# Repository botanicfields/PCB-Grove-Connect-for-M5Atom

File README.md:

# PCB-Grove-for-M5Atom
a PCB to add 3 Grove Connectors to M5Atom

# M5Atom 用 GROVE コネクタ基板

M5Atom のピンソケット (GPIO) を GROVE コネクタに変換する基板です。
GROVE ケーブルによるデバイスの接続が簡単になります。

委託販売（スイッチサイエンス）：  
https://www.switch-science.com/catalog/7309/

## 1. 特徴

- 基板上のピンヘッダに M5Atom Lite/Matrix を直接接続できます。
- M5Atom の GPIO を GROVE コネクタ 3 個で取り出せます。M5Atom の Grove ポートと合わせて計 4 ポートとなります。
- M5Atom のピンソケットを、基板上のピンソケットから取り出せます。
- DC ジャック (5V) があり、USB-C ケーブルと同時または単独でも給電できます。DCジャックからの電源にはフューズがあります。
- ディップスイッチで、一部プルアップ抵抗/保護抵抗の接続/バイパスができます。

※ 動作中の電源の抜き差し (USB-C / DC ジャック) は、動作継続を保証できません。

## 2. ご注意

- M5Atom は付属しません。
- AC アダプタは付属しません。
- GROVE ケーブルは付属しません。
- ディップスイッチの切り替えには、ピンセット等が必要です。
- プリント基板単体の完成品です。ケースや足は付属しません。裏面からピンが飛び出しています。絶縁材や四隅の穴にスペーサを取り付けるなどして、負傷、静電気破壊、机などの傷を防止してください。

## 使用例
「ENV ユニット」(I2C)、「M5 用光センサ・押しボタン 5 基板」(アナログ)、「DFPlayer-Mini用 Grove 接続基板」(UART) を同時接続し、USB-C または DC 5V 電源を接続しています。動作に使用したプログラム BF-030.ino は、温度・湿度・気圧・周囲の明るさをシリアルモニタに定期的に表示する一方、押しボタンで楽曲の演奏を制御（次の曲、前の曲、音量増、音量減、USB/microSD 切替）できます。

## 3. 詳細

回路図をご確認ください。

| GROVE | pin 1 | pin 2 | pin 3 | pin 4 | 想定用途 | 備考 |
|:-:|:-|:-|:-:|:-:|:-:|:-:|
|  J3  | G21 (SCL) | G25 (SDA) | +5V | GND  | I2C | プルアップ抵抗(*1)設定可 |
|  J4  | G33 | G23, G34 | +5V | GND  | アナログ入力 | - |
|  J5  | G22 (RX) | G19 (TX) | +5V | GND  | シリアル |  保護抵抗(*2)バイパス可 |

(*1) DIP スイッチ 1, 2 を ON にすると、プルアップ抵抗 (10kΩ) が有効となります。I2C では M5Atom 内蔵のプルアップ機能があり、またデバイス側にもプルアップ抵抗があったりするため通常は不要ですが、外付けが必要な場合に使えます。
 
(*2) DIP スイッチ 3, 4 を ON にすると、保護抵抗 (1kΩ) をバイパスします。保護抵抗は、5V 系のシリアルインタフェースを 3.3V 系である M5Atom の RX に接続する場合の過電圧から保護します。3.3V 系との接続では保護抵抗をバイパスできます。3.3V で出力する TX には保護抵抗は不要と考えられますが、実験での接続ミスなどを考慮して使用することもできます。

| DIP スイッチ 番号 | 影響するピン | ON の場合 |
|:-:|:-:|:-:|
| 1 | G21 (SCL) | プルアップ抵抗 (10kΩ) を接続 |
| 2 | G25 (SDA) | プルアップ抵抗 (10kΩ) を接続 |
| 3 | G22 (RX)  | 保護抵抗(1kΩ) をバイパス |
| 4 | G19 (TX)  | 保護抵抗(1kΩ) をバイパス |

DC ジャックからの電源にはフューズ (PTC リセッタブル、保持電流 1.1A, トリップ電流 2.2A) があります。ちなみに M5Atom 内部には 5V 出力に 0.5A のフューズがあります。

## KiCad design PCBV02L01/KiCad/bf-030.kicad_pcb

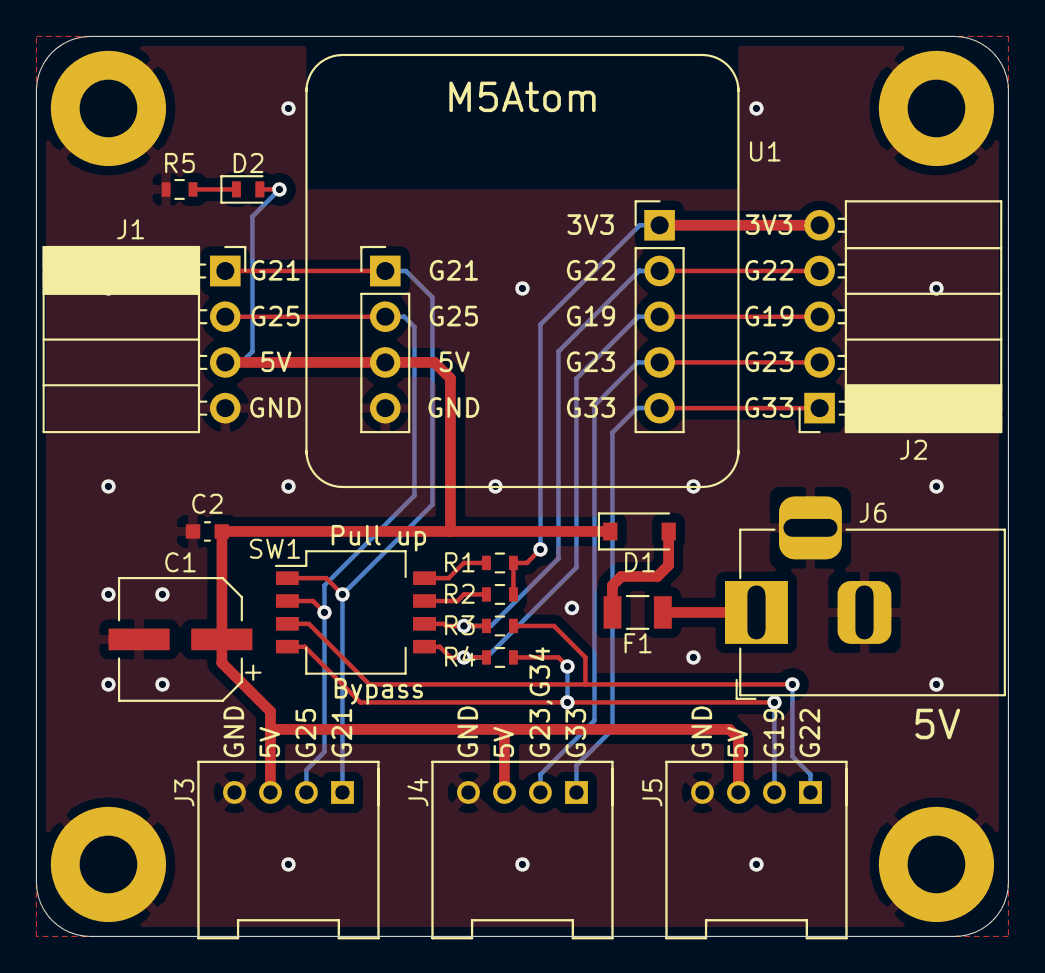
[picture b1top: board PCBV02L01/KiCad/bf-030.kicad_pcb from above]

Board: 2 copper layers, 54.0 x 50.0 mm, 18 parts (0 on the bottom side), 16 nets.

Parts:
C1: 100u; BF@CP_Elec_6.3x5.3
C2: 100n; BF@C_0603_1608Metric
D1: B5819W; BF@D_SOD-123
D2: LED; BF@LED_0603_1608Metric
F1: 1A; BF@Fuse_1206_3216Metric
J1: M5Atom-1; PinSocket_1x04_P2.54mm_Horizontal
J2: M5Atom-2; PinSocket_1x05_P2.54mm_Horizontal
J3: I2C; HW4-2.0-90D
J4: ADC; HW4-2.0-90D
J5: RXTX; HW4-2.0-90D
J6: Barrel_Jack_Switch; BF@BarrelJack_Horizontal
R1, R2: 10k; BF@R_0603_1608Metric
R3, R4: 1k; BF@R_0603_1608Metric
R5: 3.3k; BF@R_0603_1608Metric
SW1: PU-BYP; SW_DIP_SPSTx04_Slide_KingTek_DSHP04TS_W7.62mm_P1.27mm
U1: M5Atom; BF@M5Atom

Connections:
+3V3: J2.5, R1.1, R2.1, U1.9
+5V: C1.1, C2.1, D1.1, D2.2, J1.3, J3.3, J4.3, J5.3, U1.3
/G19(TX): J2.3, R4.2, SW1.5, U1.7
/G21(SCL): J1.1, J3.1, SW1.1, U1.1
/G22(RX): J2.4, R3.2, SW1.6, U1.8
/G23_G34: J2.2, J4.2, U1.6
/G25(SDA): J1.2, J3.2, SW1.2, U1.2
/G33: J2.1, J4.1, U1.5
GND: C1.2, C2.2, J1.4, J3.4, J4.4, J5.4, J6.2, J6.3, R5.1, U1.4
unnamed: D1.2, F1.1
unnamed: D2.1, R5.2
unnamed: F1.2, J6.1
unnamed: J5.1, R3.1, SW1.3
unnamed: J5.2, R4.1, SW1.4
unnamed: R1.2, SW1.8
unnamed: R2.2, SW1.7

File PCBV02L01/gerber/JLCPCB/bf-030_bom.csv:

Comment,Designator,Footprint,LCSC
100u,C1,bf:BF@CP_Elec_6.3x5.3,C134749
100n,C2,bf:BF@C_0603_1608Metric,C14663
B5819W,D1,bf:BF@D_SOD-123,C8598
LED,D2,bf:BF@LED_0603_1608Metric,C72043
1A,F1,bf:BF@Fuse_1206_3216Metric,C126818
M5Atom-1,J1,Connector_PinSocket_2.54mm:PinSocket_1x04_P2.54mm_Horizontal,
M5Atom-2,J2,Connector_PinSocket_2.54mm:PinSocket_1x05_P2.54mm_Horizontal,
I2C,J3,OPL_Connector:HW4-2.0-90D,
ADC,J4,OPL_Connector:HW4-2.0-90D,
RXTX,J5,OPL_Connector:HW4-2.0-90D,
Barrel_Jack_Switch,J6,bf:BF@BarrelJack_Horizontal,
10k,"R1,R2",bf:BF@R_0603_1608Metric,C25804
1k,"R3,R4",bf:BF@R_0603_1608Metric,C21190
3.3k,R5,bf:BF@R_0603_1608Metric,C22978
PU-BYP,SW1,Button_Switch_SMD:SW_DIP_SPSTx04_Slide_KingTek_DSHP04TS_W7.62mm_P1.27mm,C319050
M5Atom,U1,bf:BF@M5Atom,

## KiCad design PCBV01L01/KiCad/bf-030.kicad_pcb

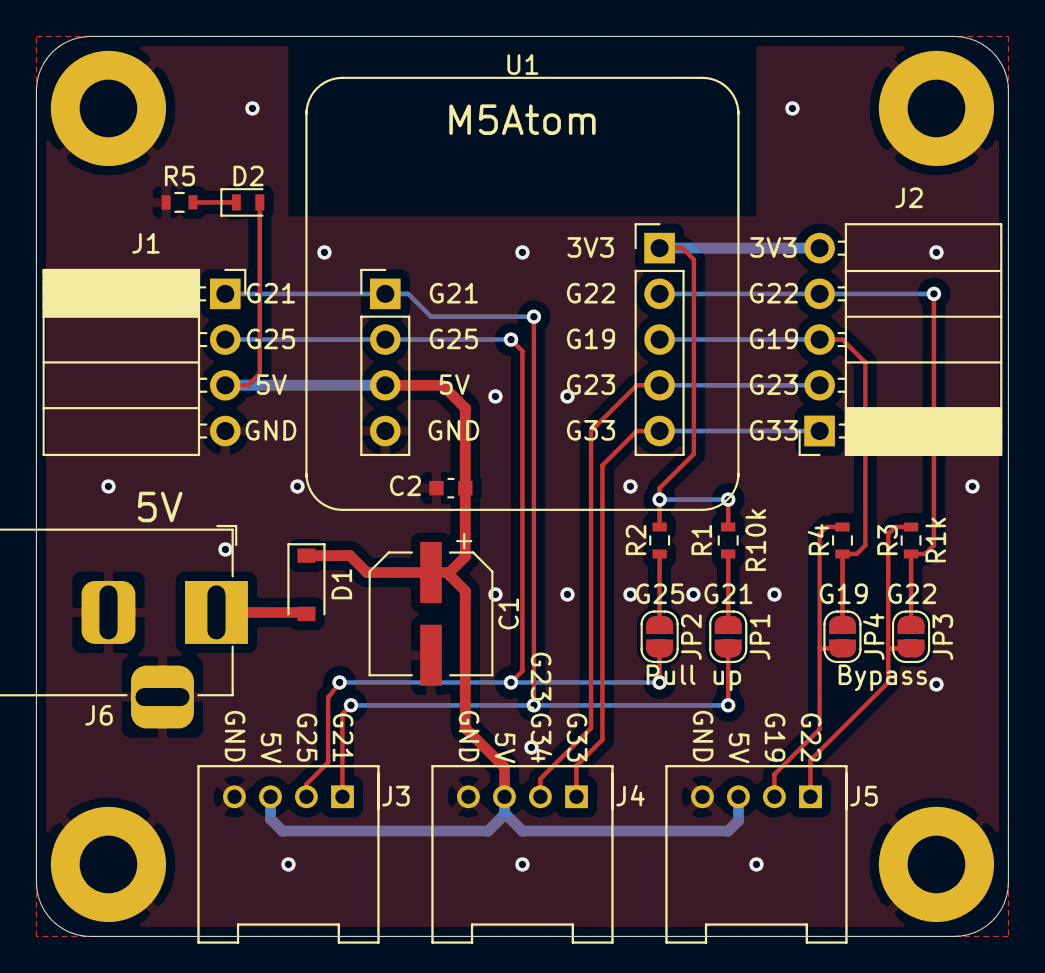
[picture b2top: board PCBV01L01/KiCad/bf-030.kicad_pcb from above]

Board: 2 copper layers, 54.0 x 50.0 mm, 20 parts (0 on the bottom side), 15 nets.

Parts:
C1: 100u; BF@CP_Elec_6.3x5.3
C2: 100n; BF@C_0603_1608Metric
D1: B5819W; BF@D_SOD-123
D2: LED; BF@LED_0603_1608Metric
J1: M5Atom-1; PinSocket_1x04_P2.54mm_Horizontal
J2: M5Atom-2; PinSocket_1x05_P2.54mm_Horizontal
J3: I2C; HW4-2.0-90D
J4: ADC; HW4-2.0-90D
J5: RXTX; HW4-2.0-90D
J6: Barrel_Jack_Switch; BF@BarrelJack_Horizontal
JP1: PU1; SolderJumper-2_P1.3mm_Open_RoundedPad1.0x1.5mm
JP2: PU2; SolderJumper-2_P1.3mm_Open_RoundedPad1.0x1.5mm
JP3: BY3; SolderJumper-2_P1.3mm_Open_RoundedPad1.0x1.5mm
JP4: BY4; SolderJumper-2_P1.3mm_Open_RoundedPad1.0x1.5mm
R1, R2: 10k; BF@R_0603_1608Metric
R3, R4: 1k; BF@R_0603_1608Metric
R5: 3.3k; BF@R_0603_1608Metric
U1: M5Atom; BF@M5Atom

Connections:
+3V3: J2.5, R1.1, R2.1, U1.9
+5V: C1.1, C2.1, D1.1, D2.2, J1.3, J3.3, J4.3, J5.3, U1.3
/G19(TX): J2.3, JP4.1, R4.2, U1.7
/G21(SCL): J1.1, J3.1, JP1.2, U1.1
/G22(RX): J2.4, JP3.1, R3.2, U1.8
/G23_G34: J2.2, J4.2, U1.6
/G25(SDA): J1.2, J3.2, JP2.2, U1.2
/G33: J2.1, J4.1, U1.5
GND: C1.2, C2.2, J1.4, J3.4, J4.4, J5.4, J6.2, J6.3, R5.1, U1.4
unnamed: D1.2, J6.1
unnamed: D2.1, R5.2
unnamed: J5.1, JP3.2, R3.1
unnamed: J5.2, JP4.2, R4.1
unnamed: JP1.1, R1.2
unnamed: JP2.1, R2.2

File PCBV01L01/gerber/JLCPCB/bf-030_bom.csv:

Comment,Designator,Footprint,LCSC
100u,C1,bf:BF@CP_Elec_6.3x5.3,C134749
100n,C2,bf:BF@C_0603_1608Metric,C14663
B5819W,D1,bf:BF@D_SOD-123,C8598
LED,D2,bf:BF@LED_0603_1608Metric,C72043
M5Atom-1,J1,Connector_PinSocket_2.54mm:PinSocket_1x04_P2.54mm_Horizontal,
M5Atom-2,J2,Connector_PinSocket_2.54mm:PinSocket_1x05_P2.54mm_Horizontal,
I2C,J3,OPL_Connector:HW4-2.0-90D,
ADC,J4,OPL_Connector:HW4-2.0-90D,
RXTX,J5,OPL_Connector:HW4-2.0-90D,
Barrel_Jack_Switch,J6,bf:BF@BarrelJack_Horizontal,
PU1,JP1,Jumper:SolderJumper-2_P1.3mm_Open_RoundedPad1.0x1.5mm,
PU2,JP2,Jumper:SolderJumper-2_P1.3mm_Open_RoundedPad1.0x1.5mm,
BY3,JP3,Jumper:SolderJumper-2_P1.3mm_Open_RoundedPad1.0x1.5mm,
BY4,JP4,Jumper:SolderJumper-2_P1.3mm_Open_RoundedPad1.0x1.5mm,
10k,"R1,R2",bf:BF@R_0603_1608Metric,C25804
1k,"R3,R4",bf:BF@R_0603_1608Metric,C21190
3.3k,R5,bf:BF@R_0603_1608Metric,C22978
M5Atom,U1,bf:BF@M5Atom,

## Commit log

2021-05-31 New
    First Upload
2021-06-05 V02L01
    revised
2021-06-06 PCB V02L01
    gerber
2021-06-26 example
    add example code
2021-06-30 doc
    add doc.pdf
2021-12-18 Update BF-030.ino
    add unsigned to "int last_ms"

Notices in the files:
PCBV01L01/KiCad/bf-030.kicad_pcb:
Copyright 2021 BotanicFields, Inc.
